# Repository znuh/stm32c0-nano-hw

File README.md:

# STM32C0-Nano Hardware Design Files
This is a very simple and cheap STM32C071 board.  

It is largely compatible to ATMega-based "Nano" boards - with 3.3V IOs:  

# Features
* Simple, very low cost (2L, all parts on top of PCB)
* Builtin USB (DFU) bootloader
* Full-speed USB, no crystal needed
(using the Clock Recovery System (CRS))
* 48MHz ARM® Cortex®-M0+ with 24KB SRAM and 128KB Flash memory
* 23+2 GPIOs with 2x SPIs, 2x UARTs, 2x I2C and lots of timer channels
* 9 analog input channels, internal voltage reference
* Fast 2.5MSps 12-bit Analog-to-digital converter (ADC)
* 2x user LEDs (not shared with other GPIOs)

# More Details
see <a href="https://znu.nz/c0">znu.nz/c0</a>

# Demo Firmware
* <a href="https://github.com/znuh/stm32-ACMtest">USB ACM Console + Blinkenlights</a>

# Note
If you build this yourself, you must set the **NBOOT_SEL** Bit in the Flash Option Bytes to **zero** (e.g. via SWD), or you cannot use **BOOT0** to invoke the bootloader during powerup.

# License
Designed by Benedikt Heinz &lt;hunz at mailbox.org&gt;

Creative Commons Attribution/Share-Alike, all text above must be included in any redistribution. See license.txt for additional details.

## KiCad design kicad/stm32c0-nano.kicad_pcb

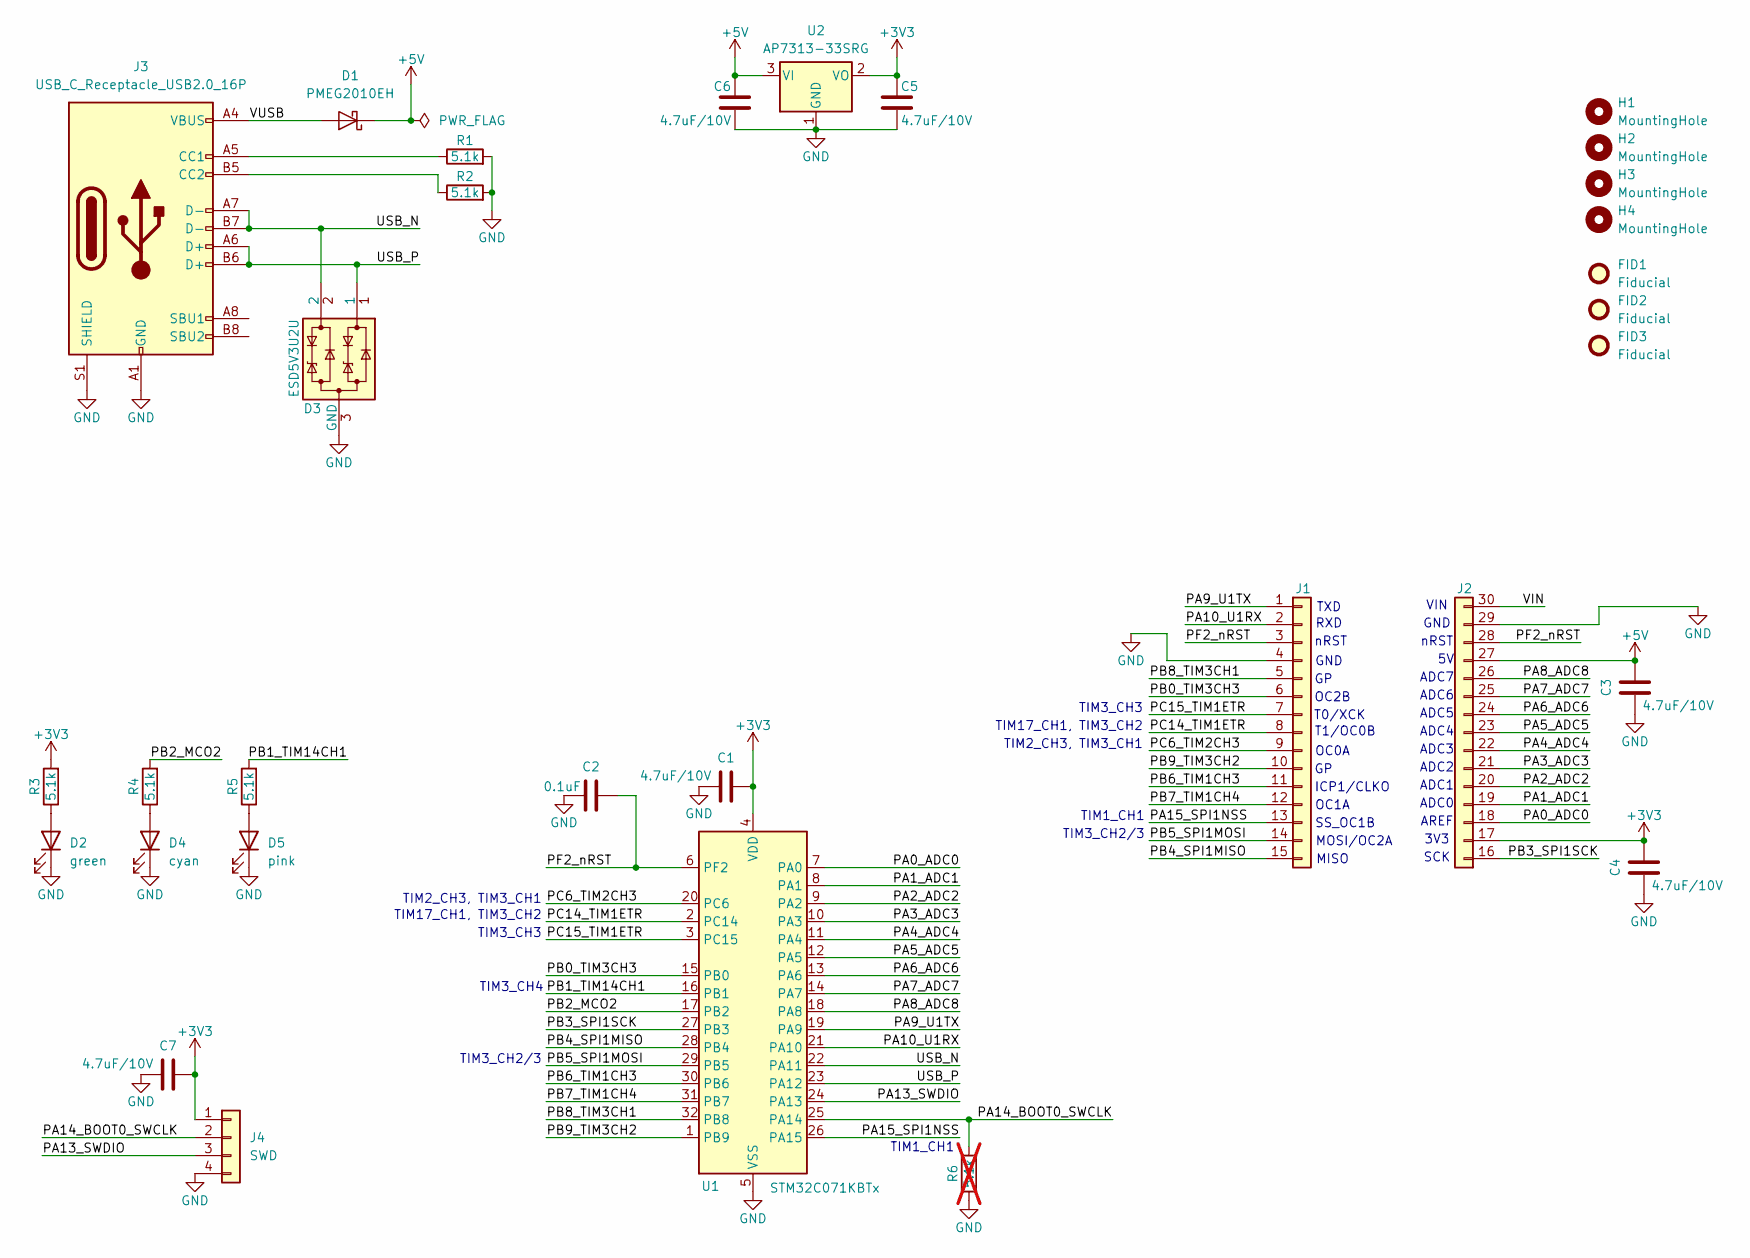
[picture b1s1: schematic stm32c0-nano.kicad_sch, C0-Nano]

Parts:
C1, C3, C4, C5, C6, C7: 4.7uF/10V; C_0402_1005Metric
C2: 0.1uF; C_0402_1005Metric
D1: PMEG2010EH; D_SOD-123F
D2: green; LED_0603_1608Metric
D3: ESD5V3U2U; Infineon_PG-TSFP-3-1
D4: cyan; LED_0603_1608Metric
D5: pink; LED_0603_1608Metric
FID1, FID2, FID3: Fiducial; Fiducial_0.5mm_Mask1mm
H1, H2, H3, H4: MountingHole; MountingHole_1.65mm
J1: Conn_01x15; PinHeader_1x15_P2.54mm_Vertical
J2: Conn_01x15_16_30; PinHeader_1x15_P2.54mm_Vertical_16_30
J3: USB_C_Receptacle_USB2.0_16P; USB_C_Receptacle_GCT_USB4105-xx-A_16P_TopMnt_Horizontal
J4: SWD; PinHeader_1x04_P2.54mm_Vertical
R1, R2, R3, R4, R5: 5.1k; R_0402_1005Metric
R6: 5.1k; R_0402_1005Metric; not fitted
U1: STM32C071KBTx; LQFP-32_7x7mm_P0.8mm
U2: AP7313-33SRG; SOT-23-3

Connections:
+3V3: C1.2, C4.2, C5.2, C7.2, J2.17, J4.1, R3.2, U1.4 (VDD), U2.2 (VO)
+5V: C3.2, C6.2, D1.1 (K), J2.27, U2.3 (VI)
/PA0_ADC0: J2.18, U1.7 (PA0)
/PA1_ADC1: J2.19, U1.8 (PA1)
/PA2_ADC2: J2.20, U1.9 (PA2)
/PA3_ADC3: J2.21, U1.10 (PA3)
/PA4_ADC4: J2.22, U1.11 (PA4)
/PA5_ADC5: J2.23, U1.12 (PA5)
/PA6_ADC6: J2.24, U1.13 (PA6)
/PA7_ADC7: J2.25, U1.14 (PA7)
/PA8_ADC8: J2.26, U1.18 (PA8)
/PA9_U1TX: J1.1, U1.19 (PA9)
/PA10_U1RX: J1.2, U1.21 (PA10)
/PA13_SWDIO: J4.3, U1.24 (PA13)
/PA14_BOOT0_SWCLK: J4.2, R6.2, U1.25 (PA14)
/PA15_SPI1NSS: J1.13, U1.26 (PA15)
/PB0_TIM3CH3: J1.6, U1.15 (PB0)
/PB1_TIM14CH1: R5.2, U1.16 (PB1)
/PB2_MCO2: R4.2, U1.17 (PB2)
/PB3_SPI1SCK: J2.16, U1.27 (PB3)
/PB4_SPI1MISO: J1.15, U1.28 (PB4)
/PB5_SPI1MOSI: J1.14, U1.29 (PB5)
/PB6_TIM1CH3: J1.11, U1.30 (PB6)
/PB7_TIM1CH4: J1.12, U1.31 (PB7)
/PB8_TIM3CH1: J1.5, U1.32 (PB8)
/PB9_TIM3CH2: J1.10, U1.1 (PB9)
/PC6_TIM2CH3: J1.9, U1.20 (PC6)
/PC14_TIM1ETR: J1.8, U1.2 (PC14)
/PC15_TIM1ETR: J1.7, U1.3 (PC15)
/PF2_nRST: C2.2, J1.3, J2.28, U1.6 (PF2)
/USB_N: D3.2, J3.A7 (D-), J3.B7 (D-), U1.22 (PA11)
/USB_P: D3.1, J3.A6 (D+), J3.B6 (D+), U1.23 (PA12)
/VIN: J2.30
/VUSB: D1.2 (A), J3.A4 (VBUS), J3.A9 (VBUS), J3.B4 (VBUS), J3.B9 (VBUS)
GND: C1.1, C2.1, C3.1, C4.1, C5.1, C6.1, C7.1, D2.1 (K), D3.3 (GND), D4.1 (K), D5.1 (K), J1.4, J2.29, J3.A1 (GND), J3.A12 (GND), J3.B1 (GND), J3.B12 (GND), J3.S1 (SHIELD), J4.4, R1.2, R2.2, R6.1, U1.5 (VSS), U2.1 (GND)
unnamed: D2.2 (A), R3.1
unnamed: D4.2 (A), R4.1
unnamed: D5.2 (A), R5.1
unnamed: J3.A5 (CC1), R1.1
unnamed: J3.B5 (CC2), R2.1

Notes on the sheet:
TIM2_CH3, TIM3_CH1
RXD
GND
TIM3_CH2/3
OC2B
nRST
OC0A
TIM17_CH1, TIM3_CH2
OC1A
ADC7
3V3
ADC6
ADC4
TIM1_CH1
MISO
ADC3
TIM3_CH3
SS_OC1B
VIN
AREF
ADC1
T1/OC0B
ADC0
T0/XCK
TIM3_CH4
ADC5
SCK
ICP1/CLKO
ADC2
MOSI/OC2A
TXD

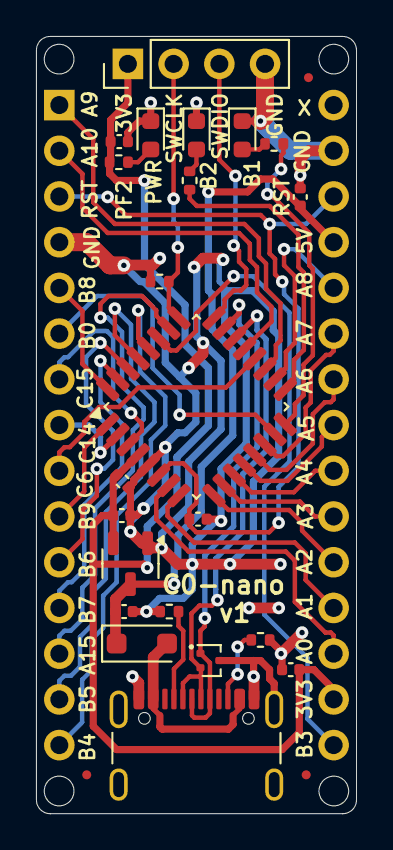
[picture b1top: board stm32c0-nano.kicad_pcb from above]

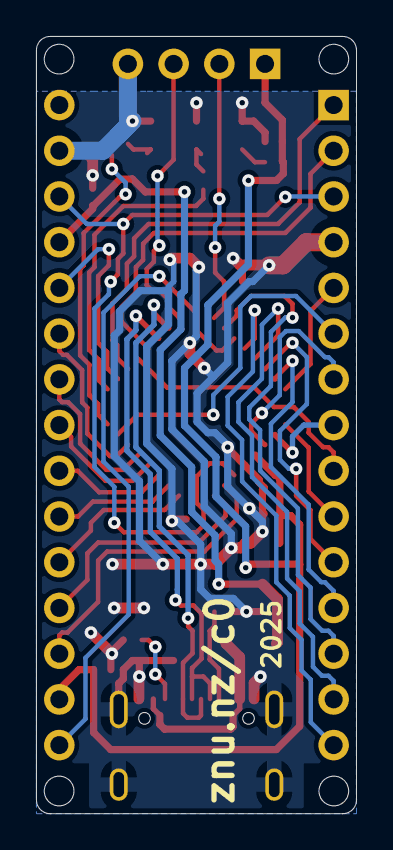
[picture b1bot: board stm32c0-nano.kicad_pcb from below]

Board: 2 copper layers, 17.8 x 43.2 mm, 31 parts (2 on the bottom side), 39 nets.

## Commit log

2025-03-11 add license
2025-03-11 add kicad files
2025-03-11 add schematics, pinouts and ibom

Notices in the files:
kicad/stm32c0-nano.kicad_pcb:
https://creativecommons.org/licenses/by-sa/4.0/deed.en
License: Creative Commons Attribution/Share-Alike 4.0
